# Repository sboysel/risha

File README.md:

# Risha

Risha is an ultra-compact, wired split ortholinear keyboard featuring:

- **36 keys**
- **Diodeless, reversible PCB** (under 102mm x 102mm)
- **Waveshare RP2040-Zero** (cutout for flush mounting)
- **Rear-facing TRRS connection**

This design prioritizes affordability, simplicity, and ease of assembly. With a total cost of around **$40 AUD**, it's an excellent choice for a budget-friendly custom keyboard.

## Features

- **Fully split layout** with only 36 keys
- **No diodes required** for a simpler build process
- **Reversible PCB** (same PCB can be used for both halves)
- **Compact design** for travel and portability
- **RP2040-Zero powered**, enabling powerful firmware support with KMK
- **TRRS interconnection** between the halves

## Getting Started

To build your own Risha, check out the following guides:

- [Buying List](docs/buying_list.md) – Everything you need to order.
- [Build Instructions](docs/build_instructions.md) – Step-by-step assembly guide.
- [Flashing Guide](docs/flashing.md) – Installing KMK firmware.

## License
This project is open-source and freely available for personal and commercial use. Contributions are welcome!

---

### Additional Resources
- [KMK Firmware](https://github.com/KMKfw/kmk_firmware) – The firmware used for Risha
- [RP2040-Zero Docs](https://www.waveshare.com/wiki/RP2040-Zero) – Official documentation for the microcontroller

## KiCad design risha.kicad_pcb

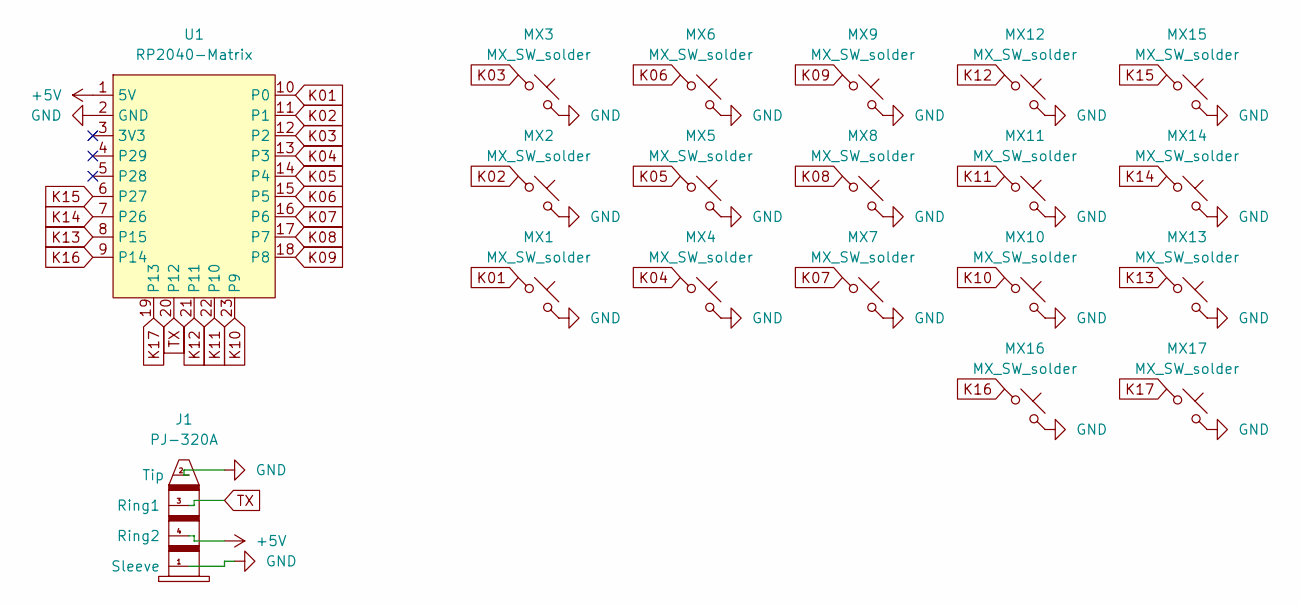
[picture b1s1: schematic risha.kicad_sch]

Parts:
J1: PJ-320A; PJ-320A_Reversible
MX1, MX2, MX3, MX4, MX5, MX6, MX7, MX8, MX9, MX10, MX11, MX12, MX13, MX14, MX15, MX16, MX17: MX_SW_solder; SW_MX_Reversible_1u
U1: RP2040-Matrix; RP2040-Matrix_AH

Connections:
+5V: J1.4 (Ring2), U1.1 (5V)
GND: J1.1 (Sleeve), J1.2 (Tip), MX1.2, MX2.2, MX3.2, MX4.2, MX5.2, MX6.2, MX7.2, MX8.2, MX9.2, MX10.2, MX11.2, MX12.2, MX13.2, MX14.2, MX15.2, MX16.2, MX17.2, U1.2 (GND)
K01: MX1.1, U1.10 (P0)
K02: MX2.1, U1.11 (P1)
K03: MX3.1, U1.12 (P2)
K04: MX4.1, U1.13 (P3)
K05: MX5.1, U1.14 (P4)
K06: MX6.1, U1.15 (P5)
K07: MX7.1, U1.16 (P6)
K08: MX8.1, U1.17 (P7)
K09: MX9.1, U1.18 (P8)
K10: MX10.1, U1.23 (P9)
K11: MX11.1, U1.22 (P10)
K12: MX12.1, U1.21 (P11)
K13: MX13.1, U1.8 (P15)
K14: MX14.1, U1.7 (P26)
K15: MX15.1, U1.6 (P27)
K16: MX16.1, U1.9 (P14)
K17: MX17.1, U1.19 (P13)
TX: J1.3 (Ring1), U1.20 (P12)

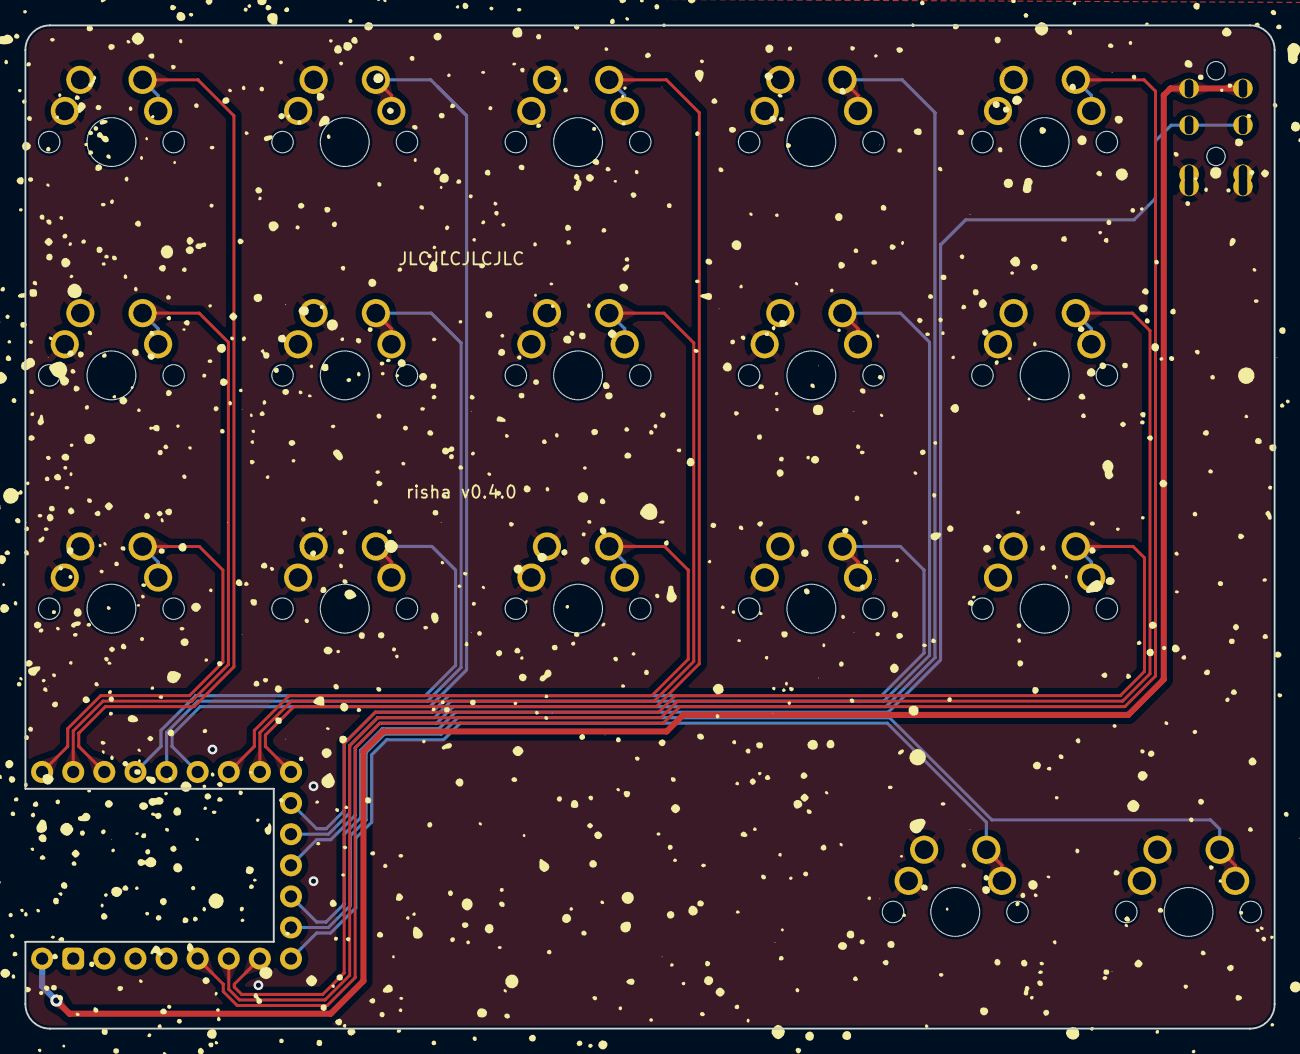
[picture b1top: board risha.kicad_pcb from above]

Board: 2 copper layers, 102.0 x 81.9 mm, 19 parts (0 on the bottom side), 20 nets.

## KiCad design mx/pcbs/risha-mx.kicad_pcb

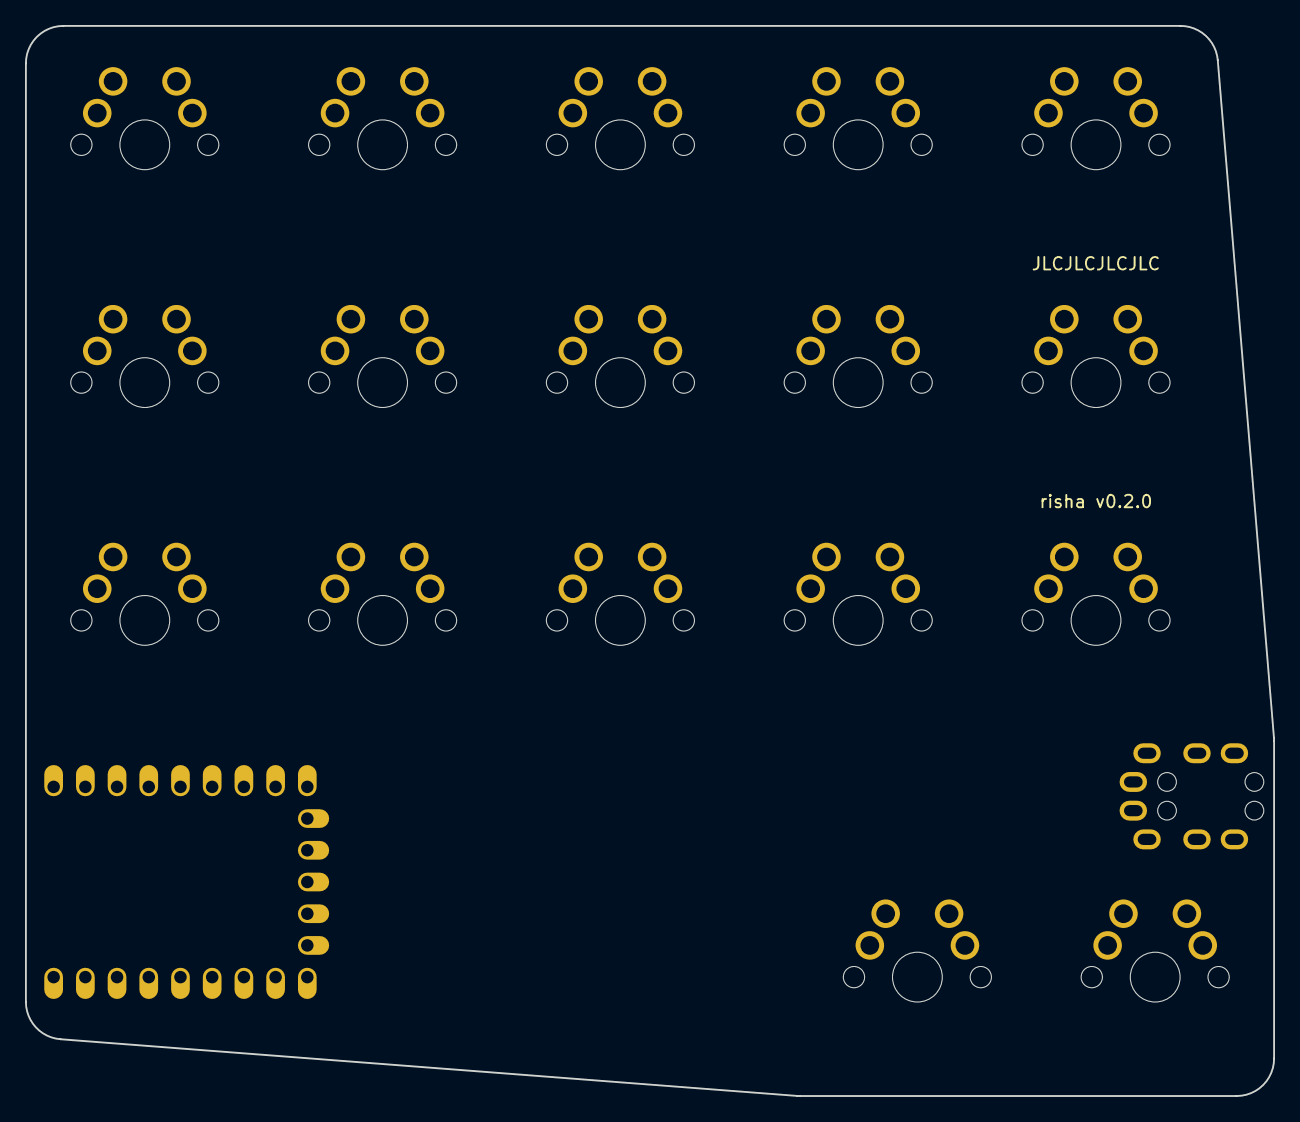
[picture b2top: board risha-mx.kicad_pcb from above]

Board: 2 copper layers, 100.0 x 85.7 mm, 18 parts (0 on the bottom side), 2 nets, no tracks yet.

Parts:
S1, S2, S3, S4, S5, S6, S7, S8, S9, S10, S11, S12, S13, S14, S15, S16, S17: MX
TRRS1: TRRS-PJ-320A-dual

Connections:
GND: S1.2, S2.2, S3.2, S4.2, S5.2, S6.2, S7.2, S8.2, S9.2, S10.2, S11.2, S12.2, S13.2, S14.2, S15.2, S16.2, S17.2, TRRS1.2
GP8: TRRS1.3, TRRS1.4
GP9: TRRS1.3, TRRS1.4

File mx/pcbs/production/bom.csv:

Designator,Footprint,Quantity,Value,LCSC Part #
,rp2040_zero_tht_pads,1,,
"S1, S10, S11, S12, S13, S14, S15, S16, S17, S18, S2, S3, S4, S5, S6, S7, S8, S9",MX,18,,
TRRS1,TRRS-PJ-320A-dual,1,TRRS-PJ-320A-dual,
"_4, _5, _6",MountingHole_2.2mm_M2_Pad_Via,3,,

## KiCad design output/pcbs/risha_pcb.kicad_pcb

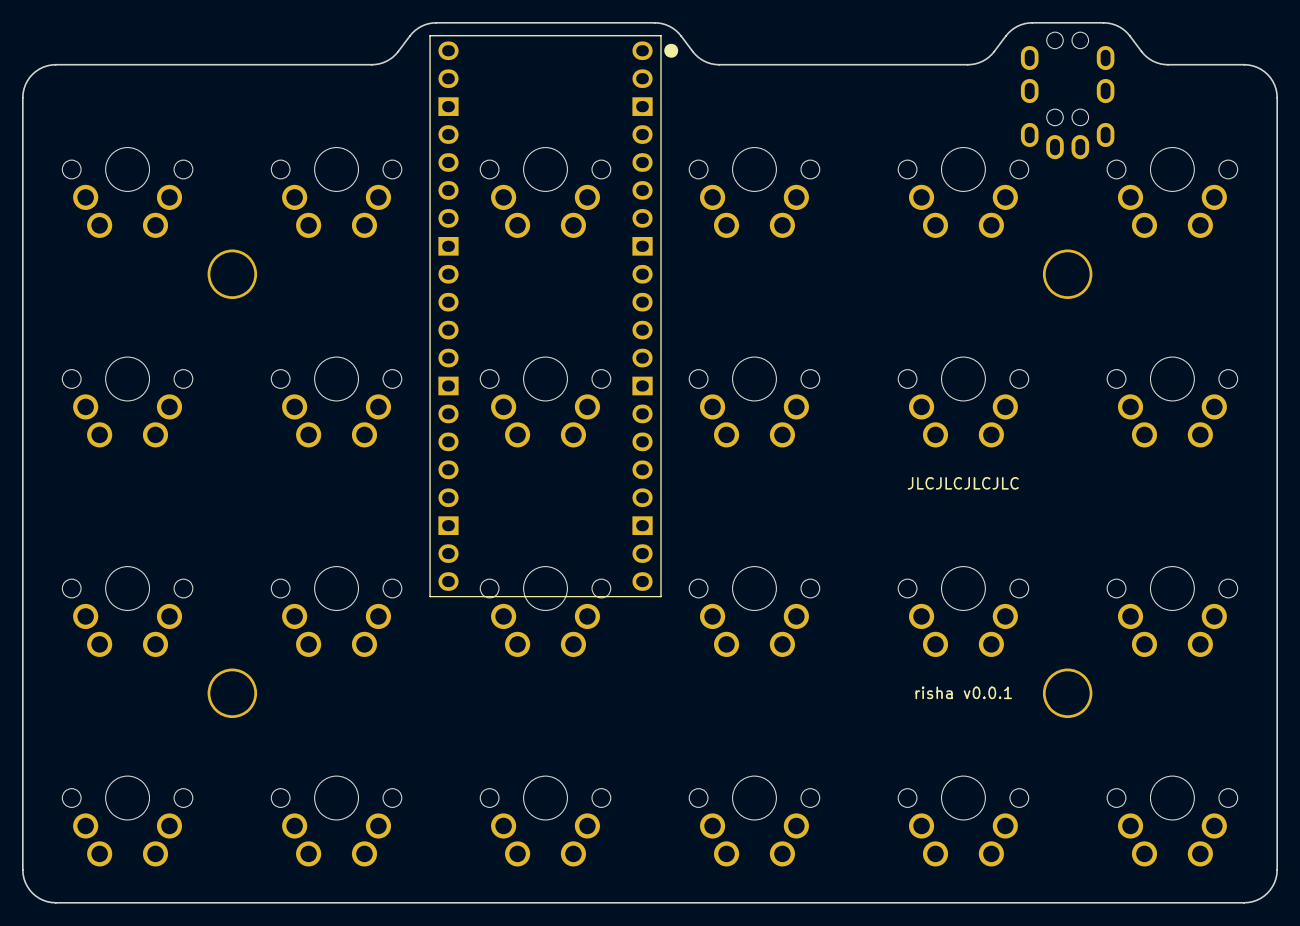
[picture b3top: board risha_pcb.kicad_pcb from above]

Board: 2 copper layers, 114.1 x 80.0 mm, 26 parts (0 on the bottom side), 4 nets, no tracks yet.

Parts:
S1, S2, S3, S4, S5, S6, S7, S8, S9, S10, S11, S12, S13, S14, S15, S16, S17, S18, S19, S20, S21, S22, S23, S24: MX
TRRS1: TRRS-PJ-320A-dual
U0: Pico; RPi_Pico_TH_oval_face_down

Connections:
3V3: TRRS1.1, U0.36
GND: S1.2, S2.2, S3.2, S4.2, S5.2, S6.2, S7.2, S8.2, S9.2, S10.2, S11.2, S12.2, S13.2, S14.2, S15.2, S16.2, S17.2, S18.2, S19.2, S20.2, S21.2, S22.2, S23.2, S24.2, TRRS1.2, U0.3, U0.8, U0.13, U0.18, U0.23, U0.28, U0.38
GP0: TRRS1.3, TRRS1.4, U0.1
GP1: TRRS1.3, TRRS1.4, U0.2

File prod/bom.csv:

Designator,Footprint,Quantity,Value,LCSC Part #
,rp2040_zero_tht_pads,1,,
"S1, S10, S11, S12, S13, S14, S15, S16, S17, S18, S2, S3, S4, S5, S6, S7, S8, S9",MX,18,,
TRRS1,TRRS-PJ-320A-dual,1,TRRS-PJ-320A-dual,
"_4, _5, _6, _7, _8",MountingHole_2.2mm_M2_Pad_Via,5,,

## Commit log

2023-04-30 xiao-based, sub 100mm^2
2023-04-30 rp2040 zero,diodeless, hotswap
2023-04-30 routing tweaks
2023-04-30 mounting holes, silkscreen text
2023-04-30 remove hotswap
2023-04-30 routing and outline tweaks
2023-04-30 move routed version of PCB into a production subdir
2023-04-30 v0.0.1 prototypes
2023-04-30 mosaic v0.0.1 (#1)
    * rp2040 zero,diodeless, hotswap
2023-05-01 v0.1.0: cleaner routing for split comm traces
2023-05-02 risha v0.0.1: Let's Split / Levinson clone with Pi Pico
2023-05-16 rename; choc and MX versions
2023-05-16 tweak outline for MX version
2023-05-16 adding image for silkscreen
2023-05-16 adding version and JLC text
2023-05-16 add readme
2023-05-17 drop mx thumb cluster a little lower
2023-05-17 outline tweaks for ergonomics
2023-05-26 rename
2023-07-15 hacky sub 100mm^2 idea for rear-facing trrs
2023-07-16 risha v0.2.0
2023-08-01 trying new choc outline
2023-08-11 converging on mx design
2023-08-12 v0.3.0 prototypes
2023-08-12 v0.3.0 (#3)
    * v0.3.0 prototypes ordered
2025-01-05 add firmware
2025-01-05 finish routing
2025-01-24 v0.4.0
2025-02-01 Updated the config to the newest version of kmk
2025-02-01 Better Build Documentation
2025-02-23 added build images
2025-02-23 adding another build image
